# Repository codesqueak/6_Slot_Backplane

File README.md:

# 6 Slot Backplane

A standard Backplane for Nascom / Gemini / 80-BUS Computers

## Introduction

A new design backplane for Nascom / Gemini / Other 80-BUS Systems

Features

* 6 Slots
* Full interrupt daisy-chaining
* Ground rails between all signals for reliability
* All signal lines clearly labelled
* Pads for Reset switch
* Pads for 5V power indicator
* Pads for Molex KK 396 power connector
* Size 21 x 16 cm (approx)

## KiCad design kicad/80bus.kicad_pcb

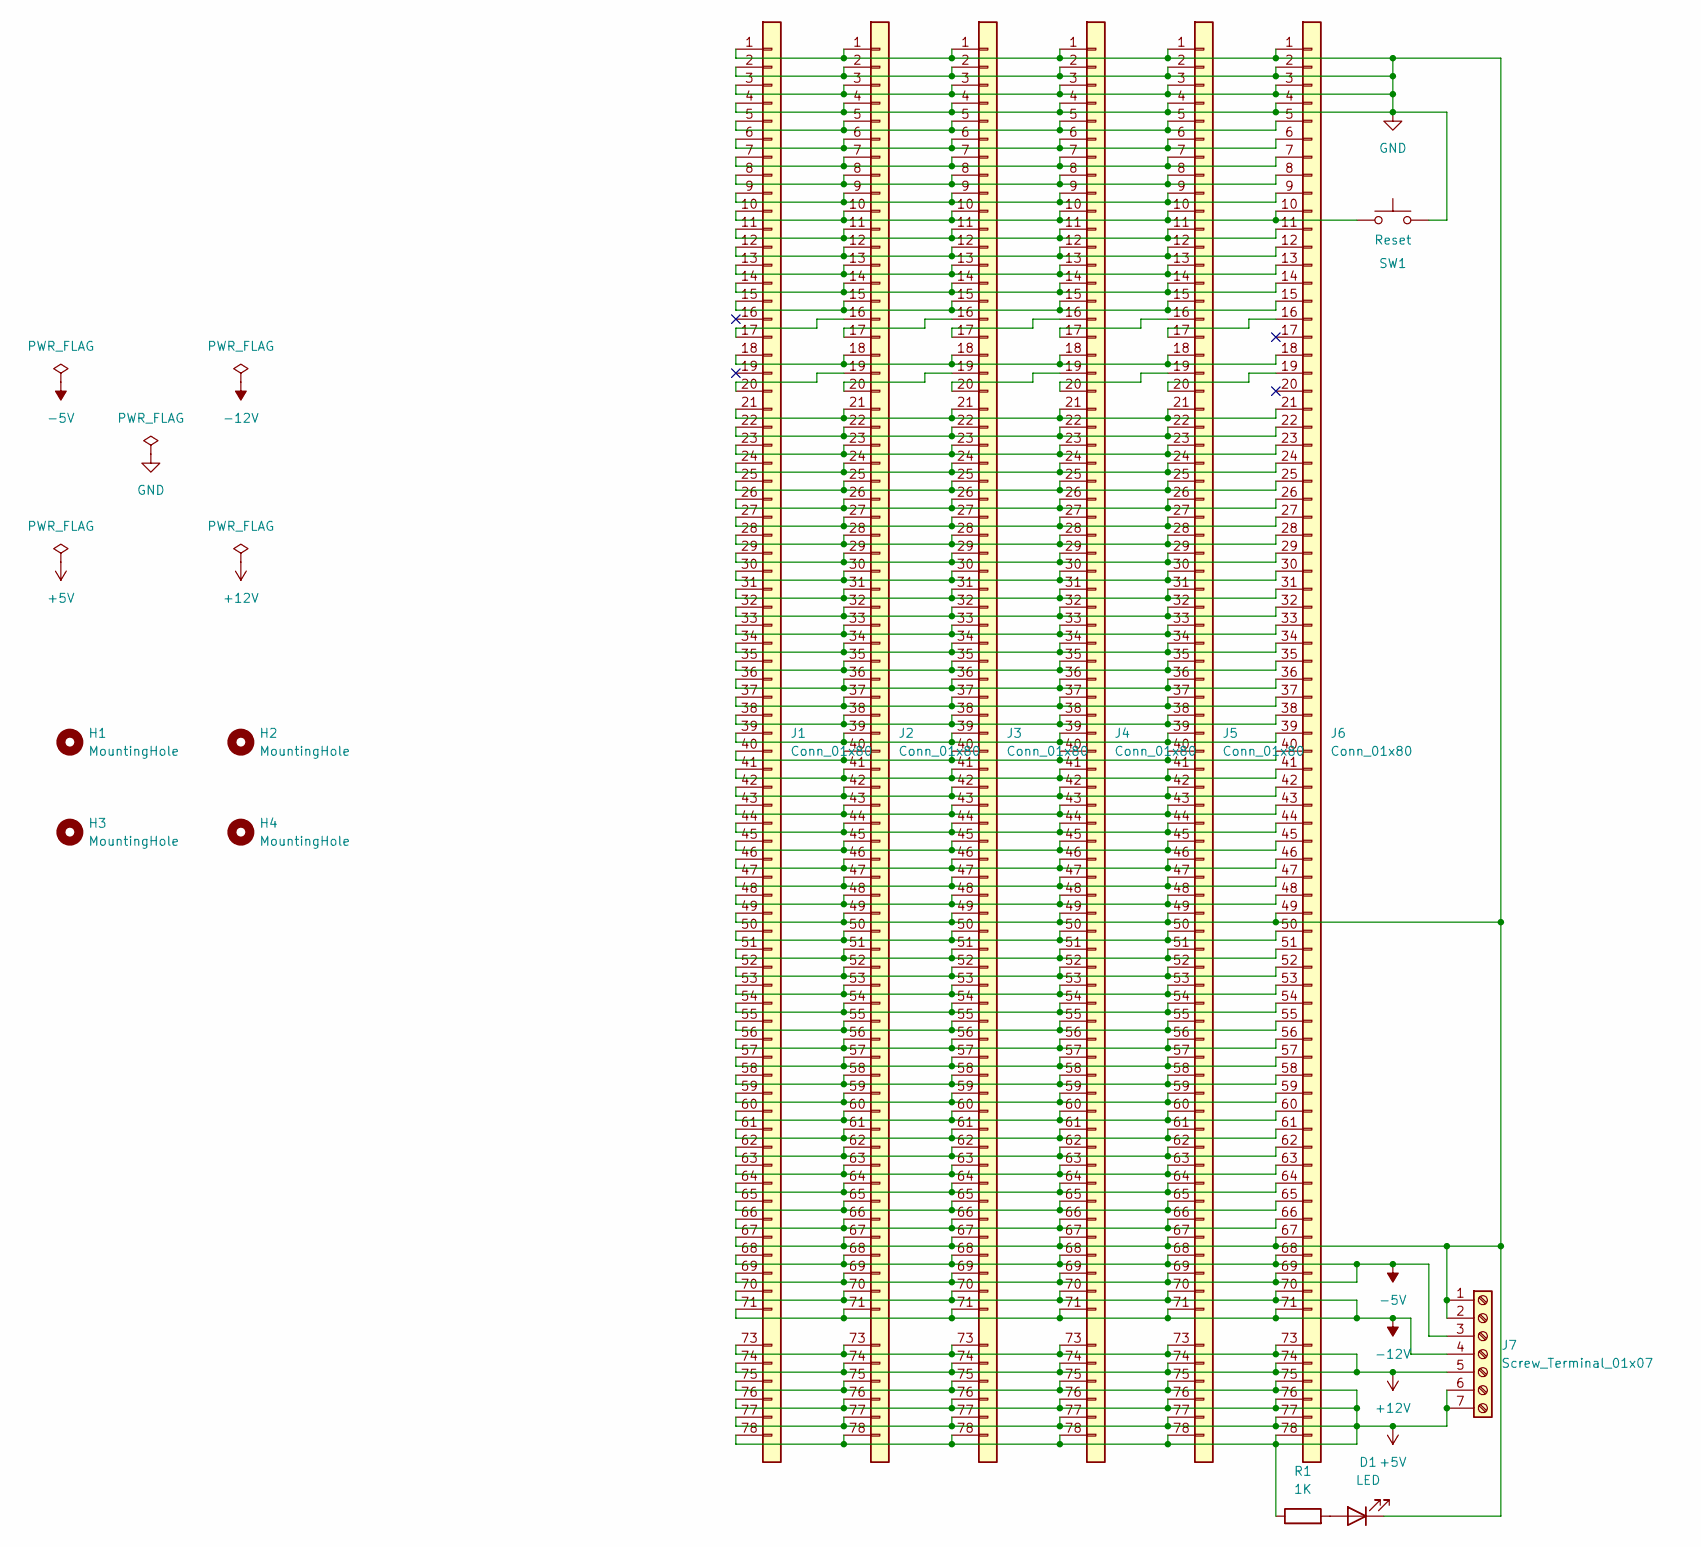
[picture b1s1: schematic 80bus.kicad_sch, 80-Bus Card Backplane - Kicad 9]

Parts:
D1: LED; LED_D3.0mm
H1, H2, H3, H4: MountingHole; MountingHole_3.5mm
J1, J2, J3, J4, J5, J6: Conn_01x80; PinHeader_1x80_P2.54mm_Vertical
J7: Screw_Terminal_01x07; Molex_KK-396_5273-07A_1x07_P3.96mm_Vertical
R1: 1K; R_Axial_DIN0309_L9.0mm_D3.2mm_P12.70mm_Horizontal
SW1: Reset; SW_PUSH_6mm_H5mm

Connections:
+5V: J1.75 (Pin_35), J1.76 (Pin_36), J1.77 (Pin_37), J1.78 (Pin_38), J2.75 (Pin_35), J2.76 (Pin_36), J2.77 (Pin_37), J2.78 (Pin_38), J3.75 (Pin_35), J3.76 (Pin_36), J3.77 (Pin_37), J3.78 (Pin_38), J4.75 (Pin_35), J4.76 (Pin_36), J4.77 (Pin_37), J4.78 (Pin_38), J5.75 (Pin_35), J5.76 (Pin_36), J5.77 (Pin_37), J5.78 (Pin_38), J6.75 (Pin_35), J6.76 (Pin_36), J6.77 (Pin_37), J6.78 (Pin_38), J7.6, J7.7, R1.1
+12V: J1.73 (Pin_33), J1.74 (Pin_34), J2.73 (Pin_33), J2.74 (Pin_34), J3.73 (Pin_33), J3.74 (Pin_34), J4.73 (Pin_33), J4.74 (Pin_34), J5.73 (Pin_33), J5.74 (Pin_34), J6.73 (Pin_33), J6.74 (Pin_34), J7.5
-5V: J1.68 (Pin_28), J1.69 (Pin_29), J2.68 (Pin_28), J2.69 (Pin_29), J3.68 (Pin_28), J3.69 (Pin_29), J4.68 (Pin_28), J4.69 (Pin_29), J5.68 (Pin_28), J5.69 (Pin_29), J6.68 (Pin_28), J6.69 (Pin_29), J7.3
-12V: J1.70 (Pin_30), J1.71 (Pin_31), J2.70 (Pin_30), J2.71 (Pin_31), J3.70 (Pin_30), J3.71 (Pin_31), J4.70 (Pin_30), J4.71 (Pin_31), J5.70 (Pin_30), J5.71 (Pin_31), J6.70 (Pin_30), J6.71 (Pin_31), J7.4
GND: D1.1 (K), J1.1, J1.2, J1.3, J1.4, J1.49 (Pin_9), J1.67 (Pin_27), J2.1, J2.2, J2.3, J2.4, J2.49 (Pin_9), J2.67 (Pin_27), J3.1, J3.2, J3.3, J3.4, J3.49 (Pin_9), J3.67 (Pin_27), J4.1, J4.2, J4.3, J4.4, J4.49 (Pin_9), J4.67 (Pin_27), J5.1, J5.2, J5.3, J5.4, J5.49 (Pin_9), J5.67 (Pin_27), J6.1, J6.2, J6.3, J6.4, J6.49 (Pin_9), J6.67 (Pin_27), J7.1, J7.2, SW1.2
unnamed: D1.2 (A), R1.2
unnamed: J1.41 (Pin_1), J2.41 (Pin_1), J3.41 (Pin_1), J4.41 (Pin_1), J5.41 (Pin_1), J6.41 (Pin_1)
unnamed: J1.42 (Pin_2), J2.42 (Pin_2), J3.42 (Pin_2), J4.42 (Pin_2), J5.42 (Pin_2), J6.42 (Pin_2)
unnamed: J1.43 (Pin_3), J2.43 (Pin_3), J3.43 (Pin_3), J4.43 (Pin_3), J5.43 (Pin_3), J6.43 (Pin_3)
unnamed: J1.44 (Pin_4), J2.44 (Pin_4), J3.44 (Pin_4), J4.44 (Pin_4), J5.44 (Pin_4), J6.44 (Pin_4)
unnamed: J1.5, J2.5, J3.5, J4.5, J5.5, J6.5
unnamed: J1.45 (Pin_5), J2.45 (Pin_5), J3.45 (Pin_5), J4.45 (Pin_5), J5.45 (Pin_5), J6.45 (Pin_5)
unnamed: J1.6, J2.6, J3.6, J4.6, J5.6, J6.6
unnamed: J1.46 (Pin_6), J2.46 (Pin_6), J3.46 (Pin_6), J4.46 (Pin_6), J5.46 (Pin_6), J6.46 (Pin_6)
unnamed: J1.7, J2.7, J3.7, J4.7, J5.7, J6.7
unnamed: J1.47 (Pin_7), J2.47 (Pin_7), J3.47 (Pin_7), J4.47 (Pin_7), J5.47 (Pin_7), J6.47 (Pin_7)
unnamed: J1.8, J2.8, J3.8, J4.8, J5.8, J6.8
unnamed: J1.48 (Pin_8), J2.48 (Pin_8), J3.48 (Pin_8), J4.48 (Pin_8), J5.48 (Pin_8), J6.48 (Pin_8)
unnamed: J1.9, J2.9, J3.9, J4.9, J5.9, J6.9
unnamed: J1.10, J2.10, J3.10, J4.10, J5.10, J6.10, SW1.1
unnamed: J1.50 (Pin_10), J2.50 (Pin_10), J3.50 (Pin_10), J4.50 (Pin_10), J5.50 (Pin_10), J6.50 (Pin_10)
unnamed: J1.11, J2.11, J3.11, J4.11, J5.11, J6.11
unnamed: J1.51 (Pin_11), J2.51 (Pin_11), J3.51 (Pin_11), J4.51 (Pin_11), J5.51 (Pin_11), J6.51 (Pin_11)
unnamed: J1.12, J2.12, J3.12, J4.12, J5.12, J6.12
unnamed: J1.52 (Pin_12), J2.52 (Pin_12), J3.52 (Pin_12), J4.52 (Pin_12), J5.52 (Pin_12), J6.52 (Pin_12)
unnamed: J1.13, J2.13, J3.13, J4.13, J5.13, J6.13
unnamed: J1.53 (Pin_13), J2.53 (Pin_13), J3.53 (Pin_13), J4.53 (Pin_13), J5.53 (Pin_13), J6.53 (Pin_13)
unnamed: J1.14, J2.14, J3.14, J4.14, J5.14, J6.14
unnamed: J1.54 (Pin_14), J2.54 (Pin_14), J3.54 (Pin_14), J4.54 (Pin_14), J5.54 (Pin_14), J6.54 (Pin_14)
unnamed: J1.15, J2.15, J3.15, J4.15, J5.15, J6.15
unnamed: J1.55 (Pin_15), J2.55 (Pin_15), J3.55 (Pin_15), J4.55 (Pin_15), J5.55 (Pin_15), J6.55 (Pin_15)
unnamed: J1.56 (Pin_16), J2.56 (Pin_16), J3.56 (Pin_16), J4.56 (Pin_16), J5.56 (Pin_16), J6.56 (Pin_16)
unnamed: J1.17, J2.16
unnamed: J1.57 (Pin_17), J2.57 (Pin_17), J3.57 (Pin_17), J4.57 (Pin_17), J5.57 (Pin_17), J6.57 (Pin_17)
unnamed: J1.18, J2.18, J3.18, J4.18, J5.18, J6.18
unnamed: J1.58 (Pin_18), J2.58 (Pin_18), J3.58 (Pin_18), J4.58 (Pin_18), J5.58 (Pin_18), J6.58 (Pin_18)
unnamed: J1.59 (Pin_19), J2.59 (Pin_19), J3.59 (Pin_19), J4.59 (Pin_19), J5.59 (Pin_19), J6.59 (Pin_19)
unnamed: J1.20, J2.19
unnamed: J1.60 (Pin_20), J2.60 (Pin_20), J3.60 (Pin_20), J4.60 (Pin_20), J5.60 (Pin_20), J6.60 (Pin_20)
unnamed: J1.21, J2.21, J3.21, J4.21, J5.21, J6.21
unnamed: J1.61 (Pin_21), J2.61 (Pin_21), J3.61 (Pin_21), J4.61 (Pin_21), J5.61 (Pin_21), J6.61 (Pin_21)
unnamed: J1.22, J2.22, J3.22, J4.22, J5.22, J6.22
unnamed: J1.62 (Pin_22), J2.62 (Pin_22), J3.62 (Pin_22), J4.62 (Pin_22), J5.62 (Pin_22), J6.62 (Pin_22)
unnamed: J1.23, J2.23, J3.23, J4.23, J5.23, J6.23
unnamed: J1.63 (Pin_23), J2.63 (Pin_23), J3.63 (Pin_23), J4.63 (Pin_23), J5.63 (Pin_23), J6.63 (Pin_23)
unnamed: J1.24, J2.24, J3.24, J4.24, J5.24, J6.24
unnamed: J1.64 (Pin_24), J2.64 (Pin_24), J3.64 (Pin_24), J4.64 (Pin_24), J5.64 (Pin_24), J6.64 (Pin_24)
unnamed: J1.25, J2.25, J3.25, J4.25, J5.25, J6.25
unnamed: J1.65 (Pin_25), J2.65 (Pin_25), J3.65 (Pin_25), J4.65 (Pin_25), J5.65 (Pin_25), J6.65 (Pin_25)
unnamed: J1.26, J2.26, J3.26, J4.26, J5.26, J6.26
unnamed: J1.66 (Pin_26), J2.66 (Pin_26), J3.66 (Pin_26), J4.66 (Pin_26), J5.66 (Pin_26), J6.66 (Pin_26)
unnamed: J1.27, J2.27, J3.27, J4.27, J5.27, J6.27
unnamed: J1.28, J2.28, J3.28, J4.28, J5.28, J6.28
unnamed: J1.29, J2.29, J3.29, J4.29, J5.29, J6.29
unnamed: J1.30, J2.30, J3.30, J4.30, J5.30, J6.30
unnamed: J1.31, J2.31, J3.31, J4.31, J5.31, J6.31
unnamed: J1.32, J2.32, J3.32, J4.32, J5.32, J6.32
unnamed: J1.33, J2.33, J3.33, J4.33, J5.33, J6.33
unnamed: J1.34, J2.34, J3.34, J4.34, J5.34, J6.34
unnamed: J1.35, J2.35, J3.35, J4.35, J5.35, J6.35
unnamed: J1.36, J2.36, J3.36, J4.36, J5.36, J6.36
unnamed: J1.37, J2.37, J3.37, J4.37, J5.37, J6.37
unnamed: J1.38, J2.38, J3.38, J4.38, J5.38, J6.38
unnamed: J1.39, J2.39, J3.39, J4.39, J5.39, J6.39
unnamed: J1.40, J2.40, J3.40, J4.40, J5.40, J6.40
unnamed: J2.17, J3.16
unnamed: J2.20, J3.19
unnamed: J3.17, J4.16
unnamed: J3.20, J4.19
unnamed: J4.17, J5.16
unnamed: J4.20, J5.19
unnamed: J5.17, J6.16
unnamed: J5.20, J6.19

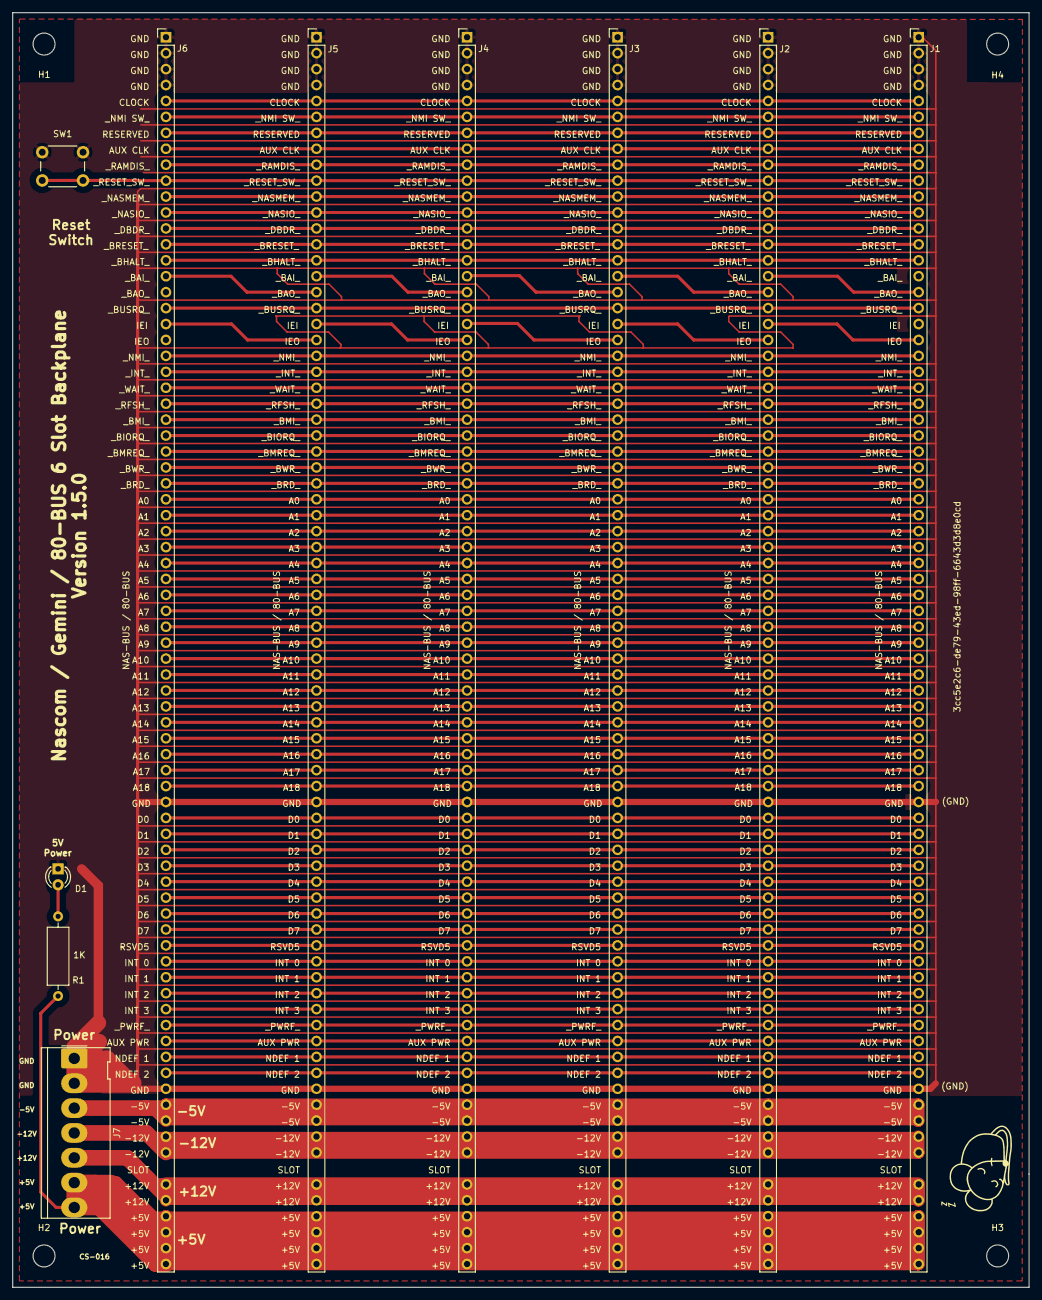
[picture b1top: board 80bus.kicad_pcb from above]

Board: 2 copper layers, 162.0 x 203.2 mm, 16 parts (1 on the bottom side), 73 nets.

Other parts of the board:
G1: LOGO; sleepymouse_very_small
G001: LOGO; qr code

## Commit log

2024-02-17 Initial update
2024-06-23 Add mounting holes
2024-10-13 Kicad, enhanced power, moved mount holes
2024-10-13 New image
2025-04-23 Kicad 9 and Docs
